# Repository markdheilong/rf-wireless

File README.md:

# rf-wireless

KiCAD PCB designs of RF 3-way frequency splitter and frequency phase shifter.

I'll include other useful RF related projects if anyone's interested in RF related PCB design and projects.

Please submit your requests directly to me for an RF circuit you'd like made by me and I'll respond.

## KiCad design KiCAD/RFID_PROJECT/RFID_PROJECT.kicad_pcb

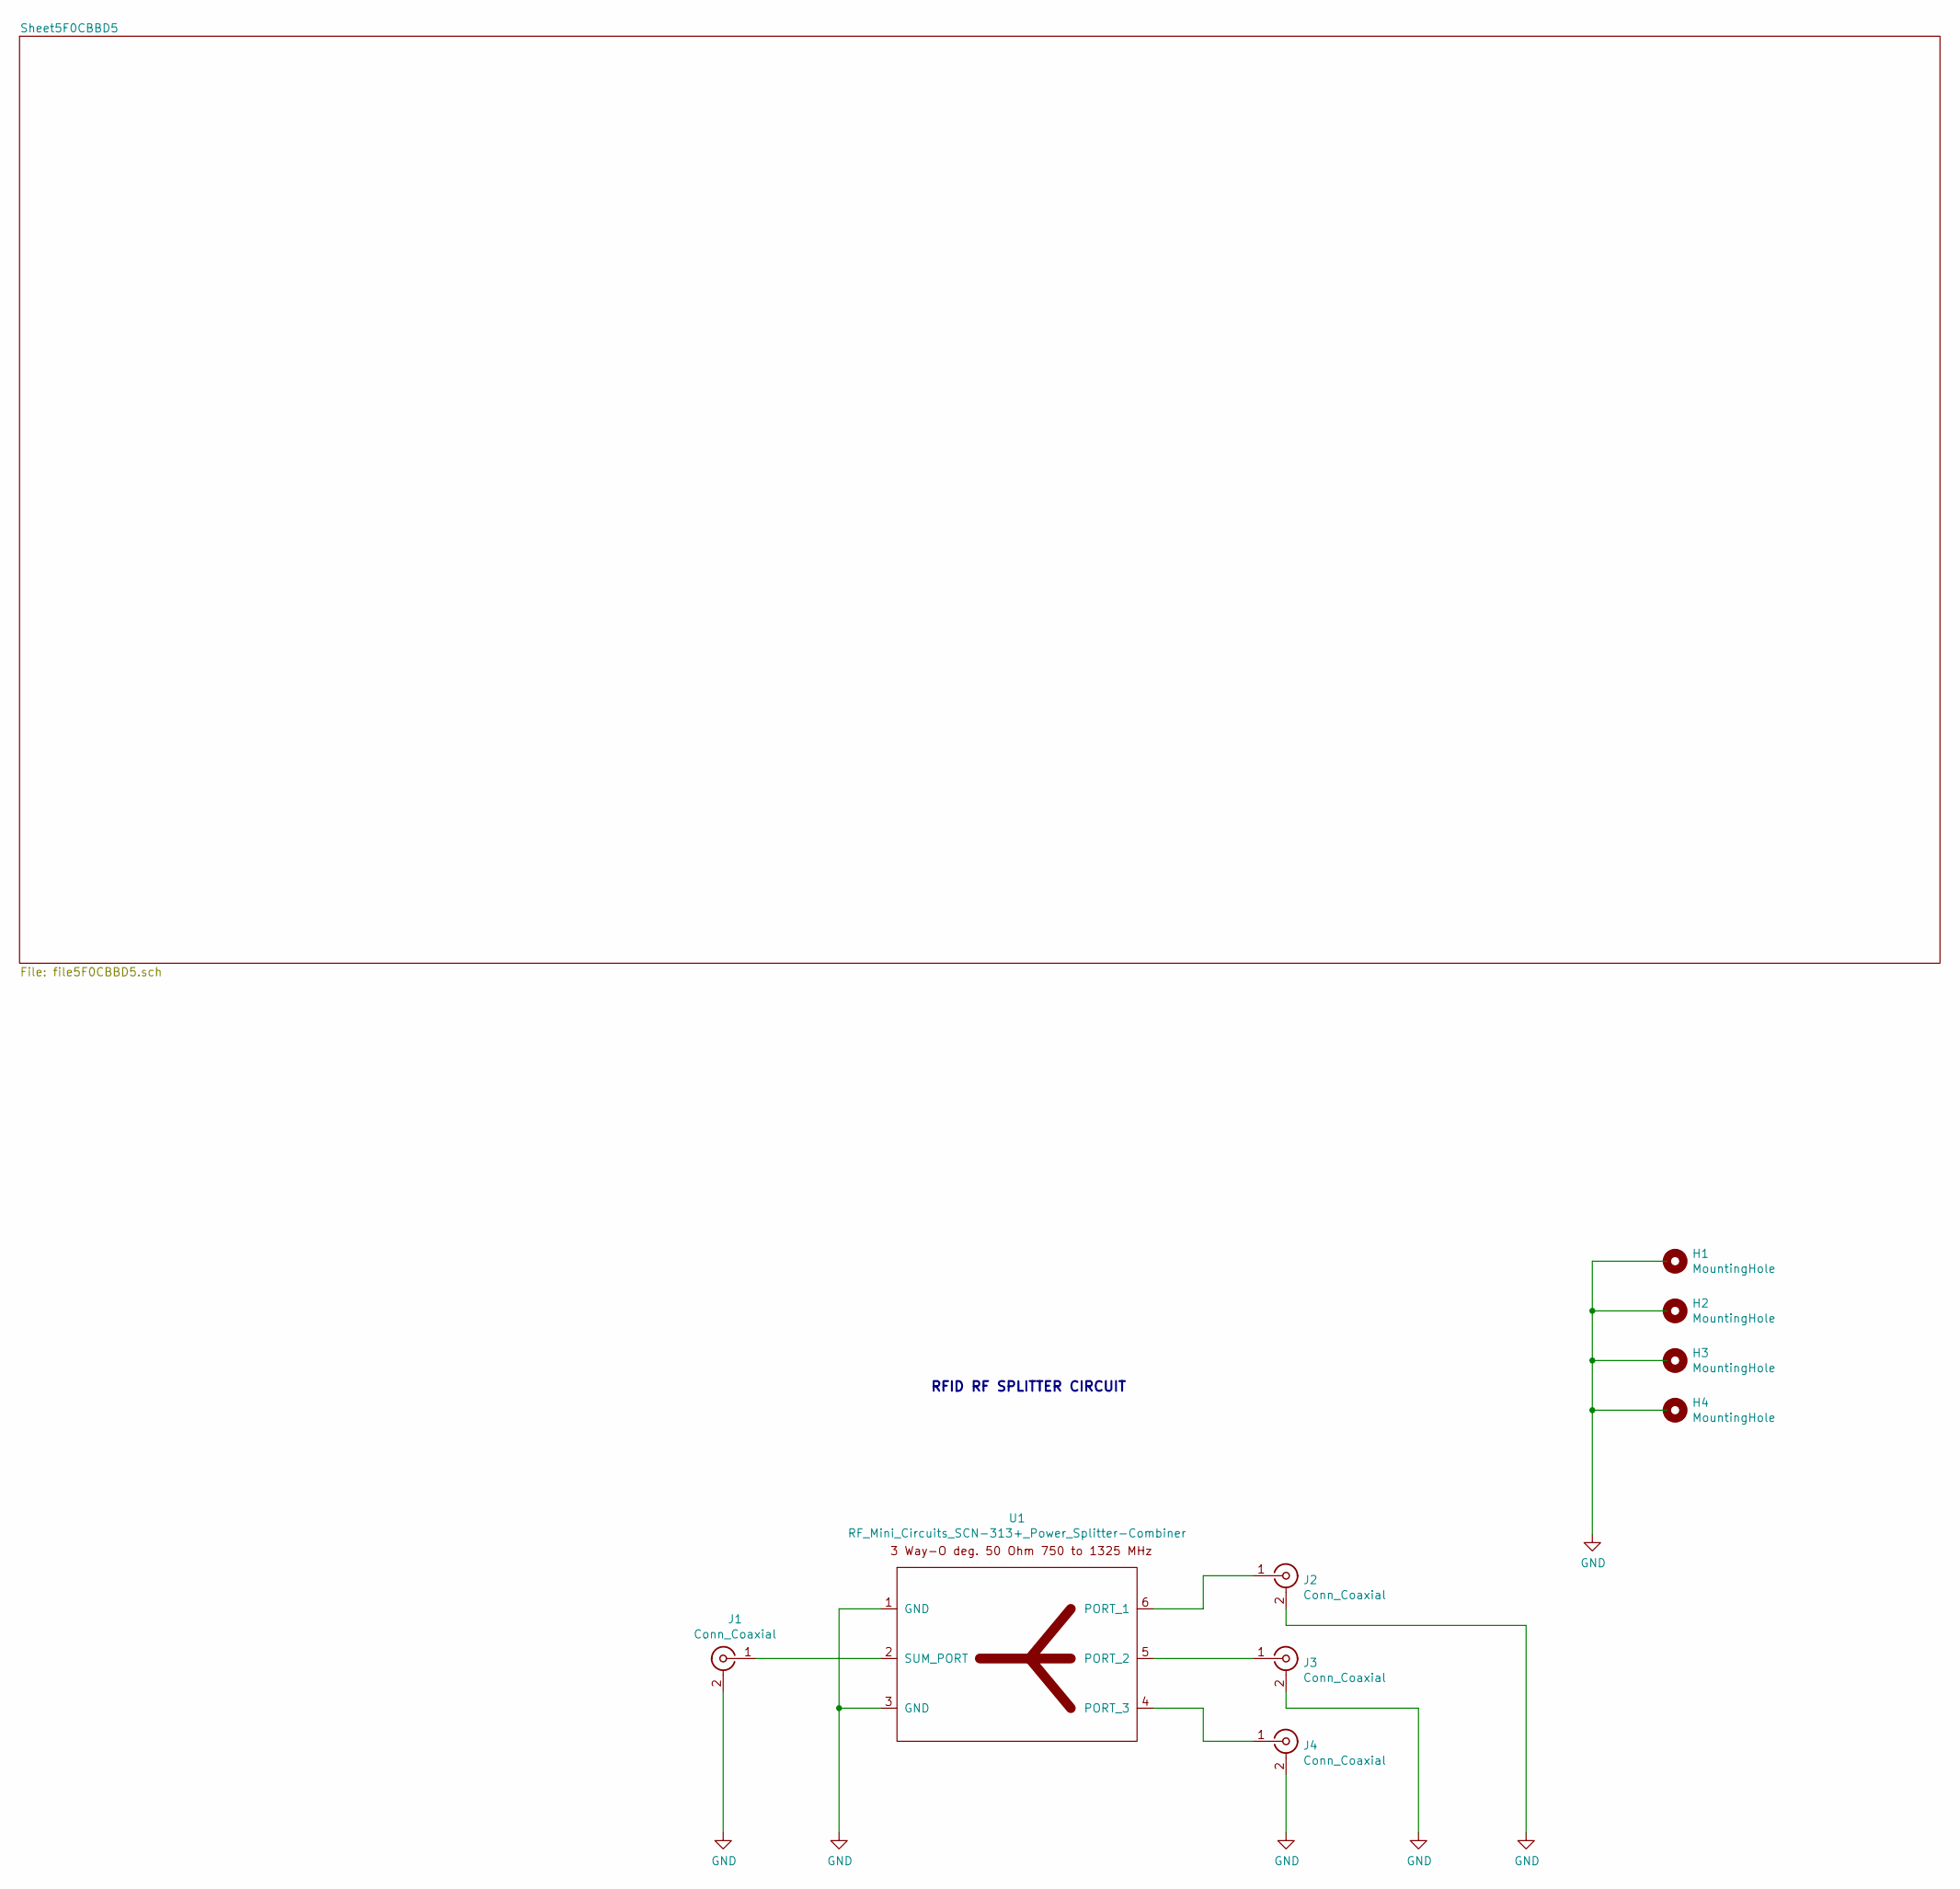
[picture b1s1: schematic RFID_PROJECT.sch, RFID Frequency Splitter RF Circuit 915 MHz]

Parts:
H1, H2, H3, H4: MountingHole; MountingHole_4.3mm_M4_Pad_Via
J1, J2, J3, J4: Conn_Coaxial; SMA_Samtec_SMA-J-P-X-ST-EM1_EdgeMount
U1: RF_Mini_Circuits_SCN-313+_Power_Splitter-Combiner; RF_Mini_Circuits_SCN-3-13+_Power_Splitter-Combiner

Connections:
GND: J1.2 (Ext), J2.2 (Ext), J3.2 (Ext), J4.2 (Ext), U1.1 (GND), U1.3 (GND)
unnamed: J1.1 (In), U1.2 (SUM_PORT)
unnamed: J2.1 (In), U1.6 (PORT_1)
unnamed: J3.1 (In), U1.5 (PORT_2)
unnamed: J4.1 (In), U1.4 (PORT_3)

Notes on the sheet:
RFID RF SPLITTER CIRCUIT

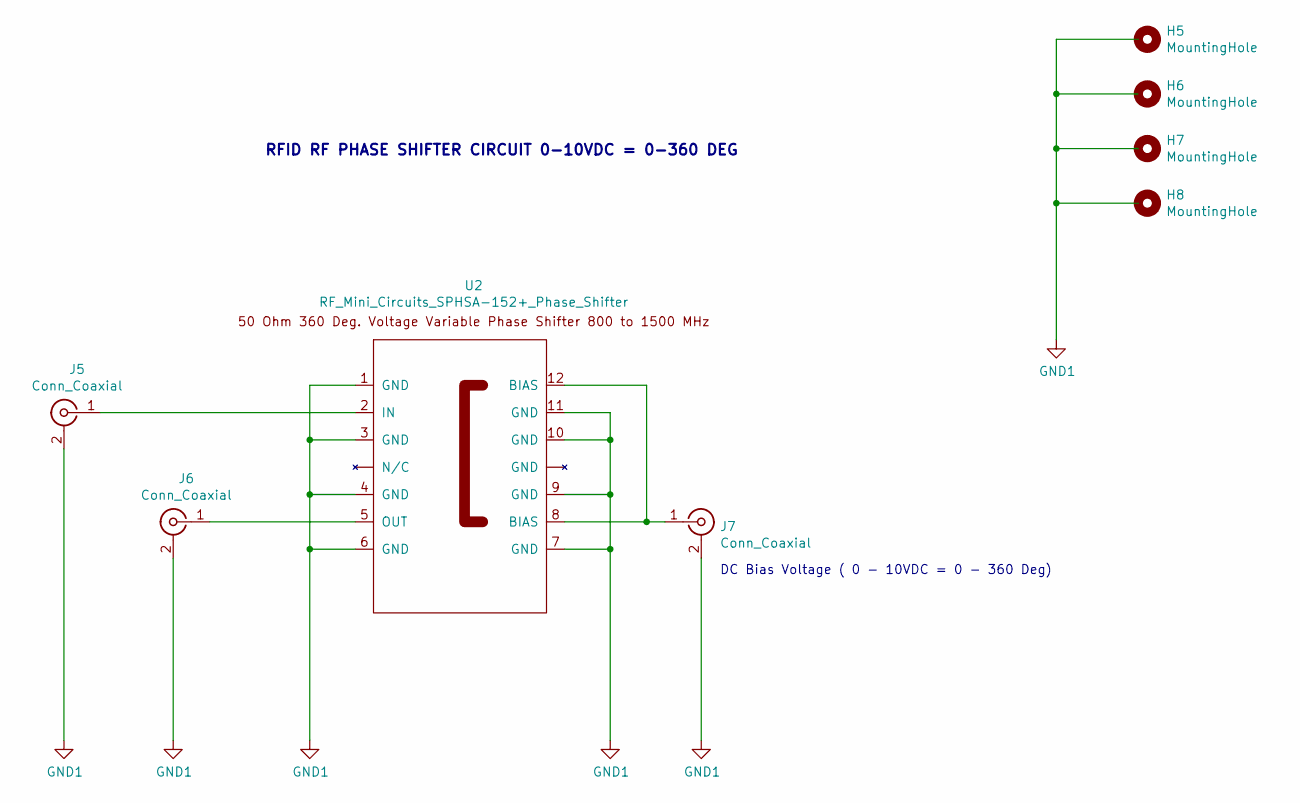
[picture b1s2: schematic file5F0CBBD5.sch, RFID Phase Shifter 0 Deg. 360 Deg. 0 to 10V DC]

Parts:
H5, H6, H7, H8: MountingHole; MountingHole_4.3mm_M4_Pad_Via
J5, J6, J7: Conn_Coaxial; SMA_Samtec_SMA-J-P-X-ST-EM1_EdgeMount
U2: RF_Mini_Circuits_SPHSA-152+_Phase_Shifter; RF_Mini_Circuits_SPHSA-152+Phase_Shifter

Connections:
GND1: J5.2 (Ext), J6.2 (Ext), J7.2 (Ext), U2.1 (GND), U2.3 (GND), U2.4 (GND), U2.6 (GND), U2.7 (GND), U2.9 (GND), U2.10 (GND), U2.11 (GND)
unnamed: J5.1 (In), U2.2 (IN)
unnamed: J6.1 (In), U2.5 (OUT)
unnamed: J7.1 (In), U2.8 (BIAS), U2.12 (BIAS)

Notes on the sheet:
DC Bias Voltage ( 0 - 10VDC = 0 - 360 Deg)
RFID RF PHASE SHIFTER CIRCUIT 0-10VDC = 0-360 DEG

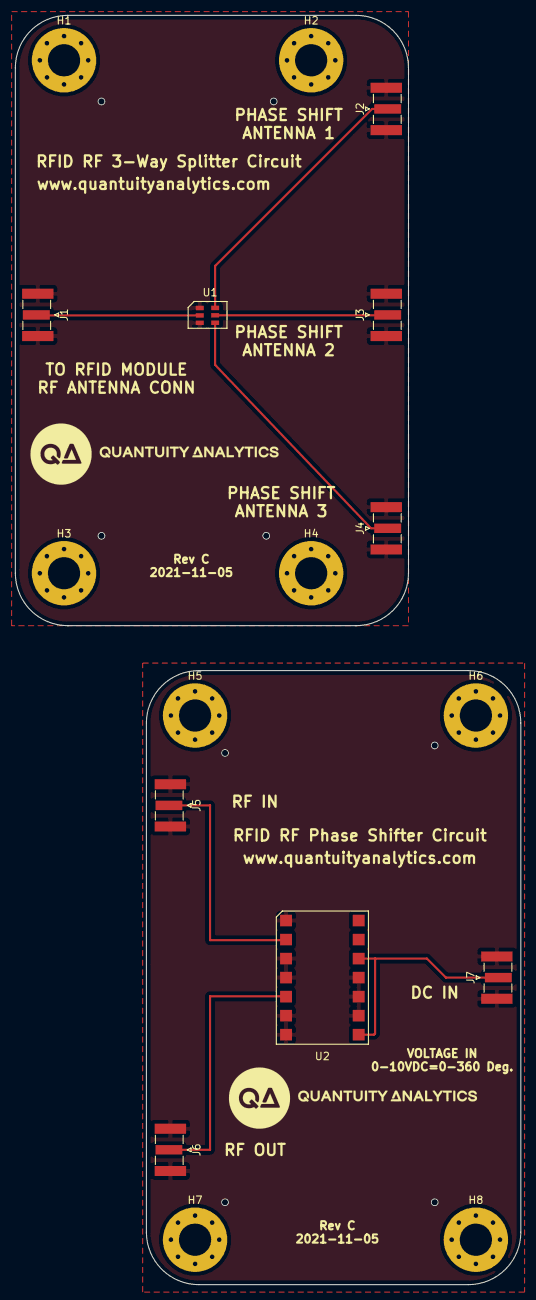
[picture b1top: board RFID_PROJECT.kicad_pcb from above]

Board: 4 copper layers, 67.5 x 169.5 mm, 17 parts (0 on the bottom side), 9 nets.

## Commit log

2022-02-02 RFID Project Phased Antenna Array Research
    Files related to RFID phase shifter and 3-way splitter circuits used for 3 antenna phased antenna array research.
2022-02-02 RFID Datasheets
    Included RFID data sheets and related research papers and documents for reference of the design.
